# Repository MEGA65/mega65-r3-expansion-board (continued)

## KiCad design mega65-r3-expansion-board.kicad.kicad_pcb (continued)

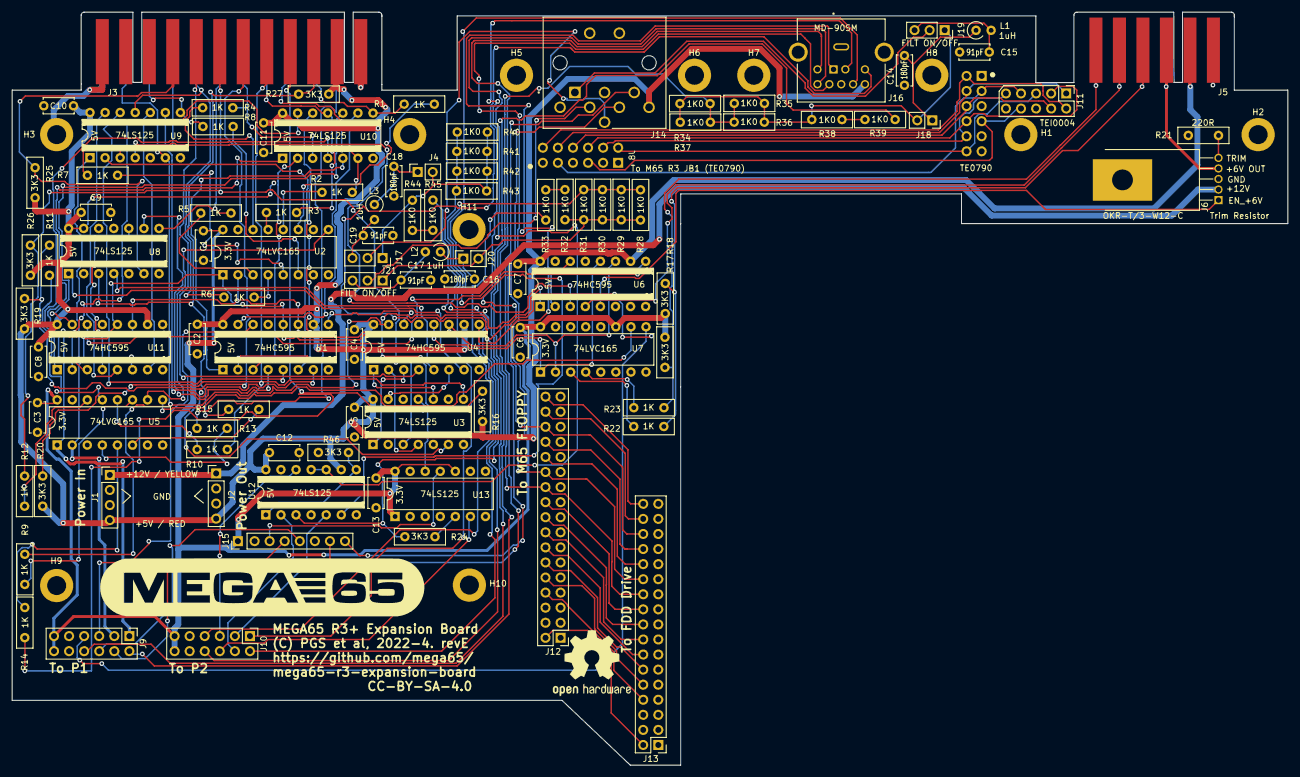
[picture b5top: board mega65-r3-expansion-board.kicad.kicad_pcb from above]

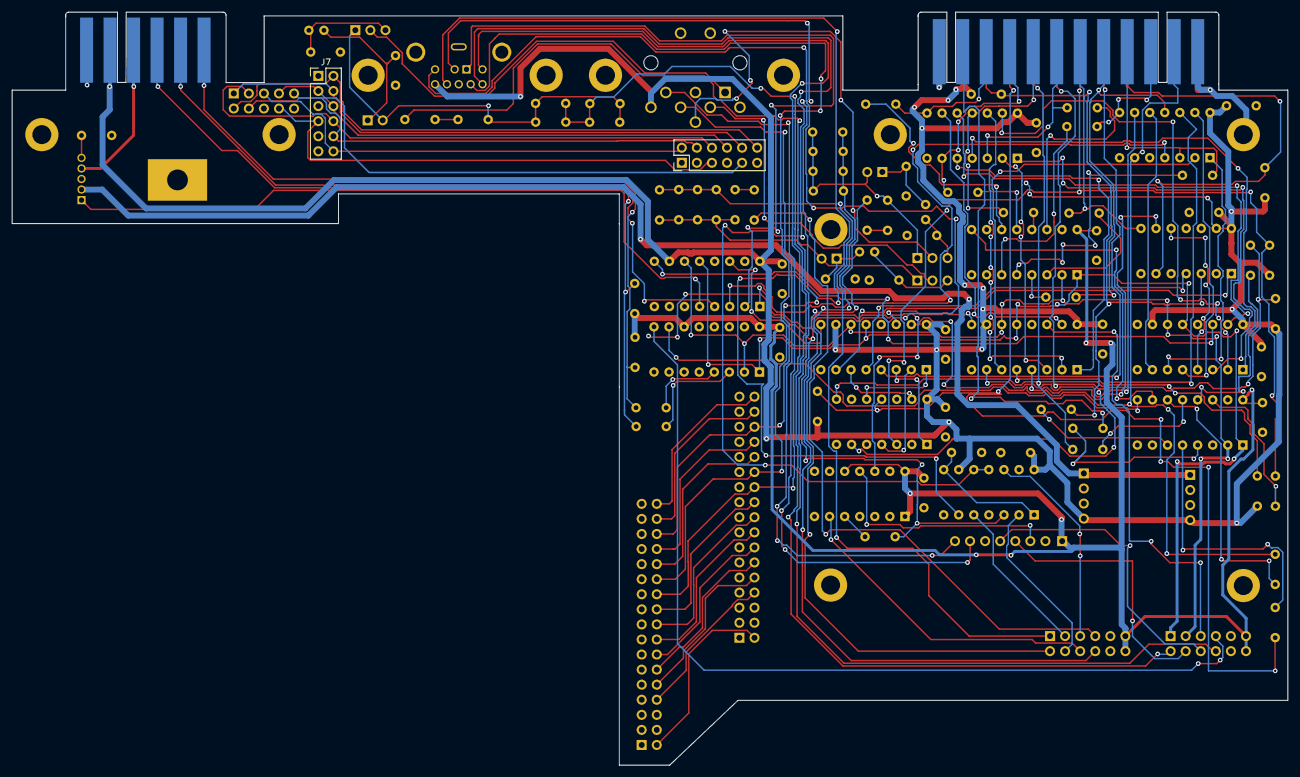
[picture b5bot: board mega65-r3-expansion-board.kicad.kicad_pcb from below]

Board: 4 copper layers, 215.0 x 126.9 mm, 114 parts (2 on the bottom side), 136 nets.

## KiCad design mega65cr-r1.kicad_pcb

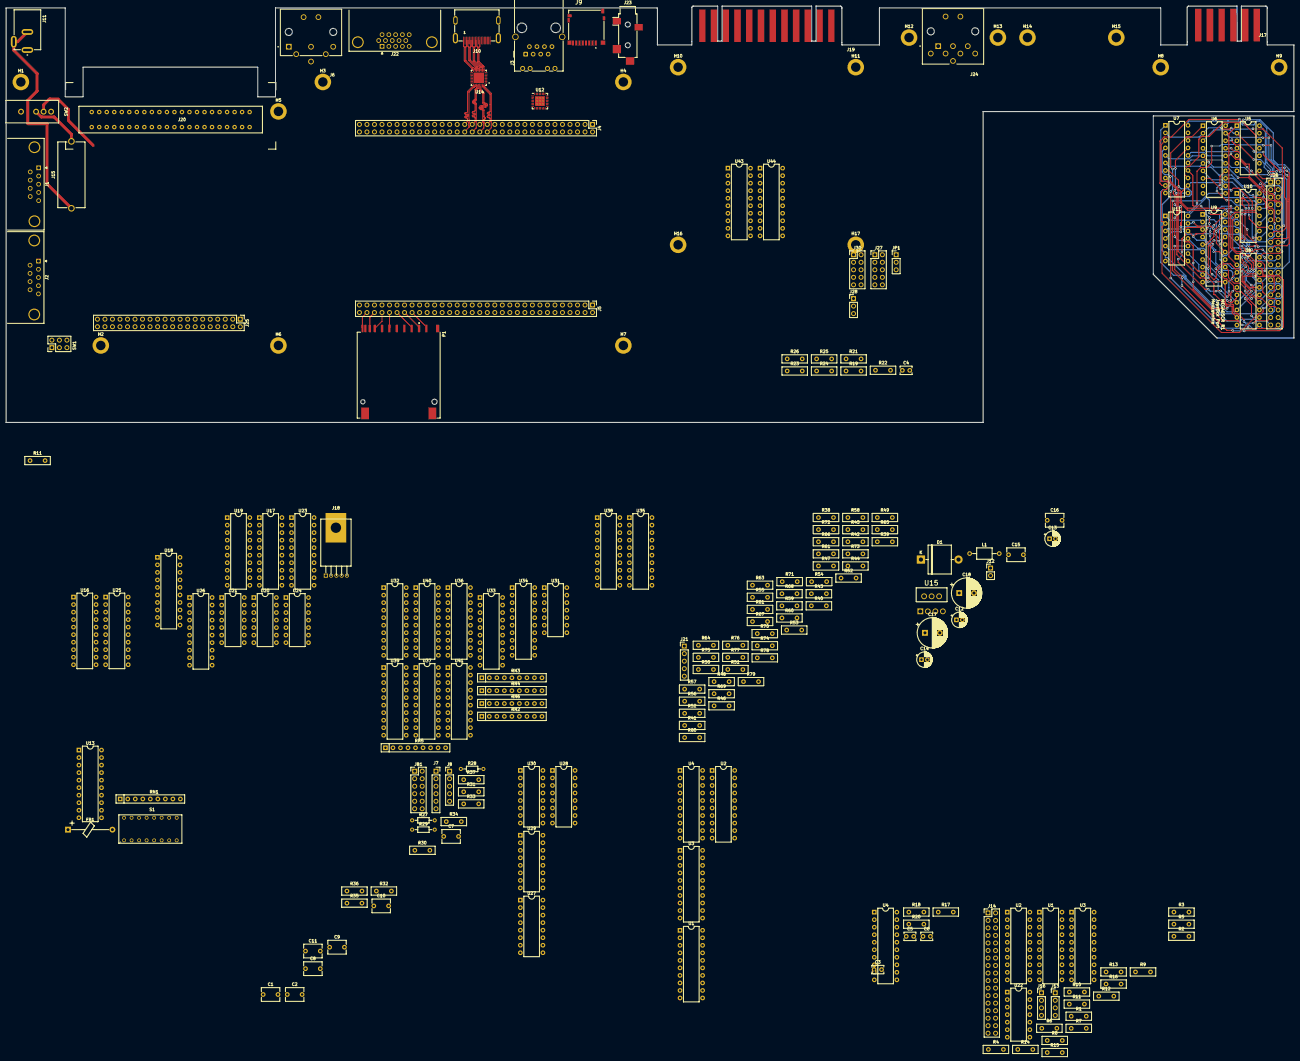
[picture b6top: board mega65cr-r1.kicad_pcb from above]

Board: 4 copper layers, 435.0 x 140.6 mm, 208 parts (0 on the bottom side), 378 nets.

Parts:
C1, C7, C10, C11: 0.1uF; C_Disc_D6.0mm_W4.4mm_P5.00mm
C2: 0.01uF, eg K103Z15Y5VE5TH5; C_Disc_D6.0mm_W4.4mm_P5.00mm
C3, C4, C5, C6: 1.2nF; C_Disc_D3.8mm_W2.6mm_P2.50mm
C8: 1uF; C_Disc_D6.0mm_W4.4mm_P5.00mm
C9: 10uF; C_Disc_D6.0mm_W4.4mm_P5.00mm
C12, C13, C14: 15uF 50V; CP_Radial_D5.0mm_P2.00mm
C15: 0.47uF eg FG28X7R1H474KRT0; C_Disc_D6.0mm_W4.4mm_P5.00mm
C16: 100nF 50V; C_Disc_D6.0mm_W4.4mm_P5.00mm
C17, C18: 180uF 16V; CP_Radial_D10.0mm_P5.00mm
D1: 5V 40V 1N5825; D_5KP_P12.70mm_Horizontal
FB1: FerriteBead FT-3AMB4ARLY-PF; Ferrite_Bead_Axial_L10.0mm_D4.5mm_P15.00mm_Horizontal
H1, H2, H3, H4, H5, H6, H7, H8, H9, H10, H11, H12, H13, H14, H15, H16, H17: MountingHole_Pad; MountingHole_3.2mm_M3_DIN965_Pad
J1, J2: DB9_Male_MountingHoles; DSUB-9_Male_Horizontal_P2.77x2.84mm_EdgePinOffset7.70mm_Hou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
J3: Wuerth_7499010121A; RJ45_Wuerth_7499010121A_Horizontal
J4: QMTECH FPGA Module U4; PinHeader_2x32_P2.54mm_Vertical
J5: QMTECH FPGA Module U5; PinHeader_2x32_P2.54mm_Vertical
J6: SDF-60J for IEC 1541 serial port; CUI_SDF-60J
J7: QMTECH JTAG; PinSocket_1x06_P2.54mm_Vertical
J8: RTC; PinHeader_1x05_P2.54mm_Vertical
J9: 1140084168 microSD Card Slot; AMPHENOL_1140084168
J10: 685119134923
J11: CON-SOCJ-2155; GRAVITECH_CON-SOCJ-2155
J12: Header for power lead to QMTECH WUKONG FPGA board; PinHeader_1x02_P2.54mm_Vertical
J13, J16: Conn_01x04_Male; PinHeader_1x04_P2.54mm_Vertical
J14: Conn_02x17_Odd_Even; PinHeader_2x17_P2.54mm_Vertical
J15: 696101000002 Fuse Holder 20mm; 696101000002
J17: C64_Tape_Port; C64-Cassette-Port-Male
J18: BA60BC0WT; TO-220-FP-5
J19: C64_User_Port; C64-User-Port-Male
J20: C64_Expansion_Port; C64-Cart-Socket-Vertical
J21: Audio Header; PinHeader_1x05_P2.54mm_Vertical
J22: DB15_Female_HighDensity_MountingHoles; DSUB-15-HD_Female_Horizontal_P2.29x1.98mm_EdgePinOffset8.35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
J23: Audio Out; Jack_3.5mm_CUI_SJ-3524-SMT_Horizontal
J24: Component A/V; CUI_SDF-80J
J25: Joystick Ports Mezannine Lower; PinHeader_2x20_P2.54mm_Vertical
J26: Joystick Ports Mezannine Upper; PinHeader_2x20_P2.54mm_Vertical
J27: USB Blaster JTAG; PinHeader_2x05_P2.54mm_Vertical
J28: UART; PinHeader_1x03_P2.54mm_Vertical
J30: Keyboard JTAG header; PinHeader_2x05_P2.54mm_Vertical
JB1: TE0790-03 JTAG + UART; PinHeader_2x06_P2.54mm_Vertical
JP1: KBD JTAG EN; PinHeader_1x03_P2.54mm_Vertical
L1: 22uH, eg SC30R22KT; L_Axial_L5.0mm_D3.6mm_P10.00mm_Horizontal_Murata_BL01RN1A2A2
P1: Full-side CD Card Slot; YAMAICHI_FPS009-2405-0
R1, R2, R3, R4, R5, R6, R7, R8, R9, R10: 1K; R_Box_L8.4mm_W2.5mm_P5.08mm
R11, R11#2, R12, R13, R14, R15, R16, R17, R18, R19, R20, R21, R22, R23, R24, R25, R26, R30, R31, R32, R33, R34, R35, R37: 4K7; R_Box_L8.4mm_W2.5mm_P5.08mm
R27, R28: 220; R_Axial_DIN0204_L3.6mm_D1.6mm_P7.62mm_Horizontal
R29: 6.49K 1%; R_Axial_DIN0204_L3.6mm_D1.6mm_P7.62mm_Horizontal
R36: 12K4; R_Box_L8.4mm_W2.5mm_P5.08mm
R38, R44, R50, R56, R62, R68, R74: 510R; R_Box_L8.4mm_W2.5mm_P5.08mm
R39, R45, R51, R57, R63, R69, R75: 1K0; R_Box_L8.4mm_W2.5mm_P5.08mm
R40, R46, R52, R58, R64, R70, R76: 2K0; R_Box_L8.4mm_W2.5mm_P5.08mm
R41, R47, R53, R59, R65, R71, R77: 4K0; R_Box_L8.4mm_W2.5mm_P5.08mm
R42, R48, R54, R60, R66, R72, R78: 8K0; R_Box_L8.4mm_W2.5mm_P5.08mm
R43, R49, R55, R61, R67, R73, R79: 16K0; R_Box_L8.4mm_W2.5mm_P5.08mm
R80, R81: 49R9; R_Box_L8.4mm_W2.5mm_P5.08mm
RN1, RN3, RN4, RN5, RN6: 3.3K x 8; R_Array_SIP9
RN2: 4609X-AP1-332LF 3.3Kx8; R_Array_SIP9
S1: 418117270908
SW1: Reset Button; SPUJ191500
SW2: SW_SPDT_with_shield; T103J1AVBE2
U1, U1#2, U4, U4#2, U9: 74LS373; DIP-20_W7.62mm
U2, U2#2, U3, U3#2, U6, U7, U13, U16, U17, U23, U32, U33, U34, U38, U39, U43: 74LVC374; DIP-20_W7.62mm
U5, U10, U11, U22: 74LS06N; DIP-14_W7.62mm
U8, U18, U19, U25, U26, U35, U36, U37, U40, U41, U44: 74LS374; DIP-20_W7.62mm
U12: DP83826; QFN-32-1EP_5x5mm_P0.5mm_EP3.3x3.3mm_ThermalVias
U14: PTN3363BSMP; QFN50P500X500X85-33N
U15: LM2678T-5.0; TO127P457X1016X2052-7P
U20, U21, U24: 74LS125; DIP-14_W7.62mm
U27, U28: 74LS138; DIP-16_W7.62mm
U29, U30: 74LS137; DIP-16_W7.62mm
U31: 74LS04; DIP-14_W7.62mm

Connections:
+3V3: FB1.1, J4.3, J4.4, J8.1, J25.2, J26.2, J27.4, J30.4, JB1.6, JP1.1 (A), P1.4 (VDD), R27.1, R28.1, R30.2, R31.2, RN1.1 (common), U2.20 (VCC), U2#2.20 (VCC), U3.20 (VCC), U3#2.20 (VCC), U6.20 (VCC), U7.20 (VCC), U13.20 (VCC), U16.20 (VCC), U17.20 (VCC), U23.20 (VCC), U29.16 (VCC), U32.20 (VCC), U33.20 (VCC), U34.20 (VCC), U38.20 (VCC), U39.20 (VCC), U43.20 (VCC)
+5V: C17.1, C18.1, J1.7, J2.7, J10.18 (+5VPOWER), J13.4, J16.4, J17.2, J17.B, J19.2, J20.2, J20.3, J21.3, J24.8, J25.1, J26.1, L1.2, R11.2, R11#2.2, R17.1, R18.1, R19.1, R20.1, R21.1, R22.1, R23.1, R24.1, R25.1, R26.1, RN2.1 (common), RN3.1 (common), RN4.1 (common), RN5.1 (common), RN6.1 (common), U1.20 (VCC), U1#2.20 (VCC), U4.20 (VCC), U4#2.20 (VCC), U5.14 (VCC), U8.20 (VCC), U9.20 (VCC), U10.14 (VCC), U11.14 (VCC), U14.1 (VDD), U14.18 (VDD), U15.6 (FB), U18.20 (VCC), U19.20 (VCC), U22.14 (VCC), U25.20 (VCC), U26.20 (VCC), U27.6 (E3), U27.16 (VCC), U28.16 (VCC), U29.6 (E3), U31.14 (VCC), U35.20 (VCC), U36.20 (VCC), U37.20 (VCC), U40.20 (VCC), U41.20 (VCC), U44.20 (VCC)
+12V_FUSED: C12.1, C13.1, C14.1, C15.1, J13.1, J16.1, J18.2, SW2.2 (B), U15.2 (VIN), U15.7 (SS)
/Cartridge Port/A0: J20.Y, RN6.9 (R8), U34.3 (D0), U37.19 (O7)
/Cartridge Port/A1: J20.X, RN6.8 (R7), U34.4 (D1), U37.16 (O6)
/Cartridge Port/A2: J20.W, RN6.7 (R6), U34.7 (D2), U37.15 (O5)
/Cartridge Port/A3: J20.V, RN6.6 (R5), U34.8 (D3), U37.12 (O4)
/Cartridge Port/A4: J20.U, RN6.5 (R4), U34.13 (D4), U37.9 (O3)
/Cartridge Port/A5: J20.T, RN6.4 (R3), U34.14 (D5), U37.6 (O2)
/Cartridge Port/A6: J20.S, RN6.3 (R2), U34.17 (D6), U37.5 (O1)
/Cartridge Port/A7: J20.R, RN6.2 (R1), U34.18 (D7), U37.2 (O0)
/Cartridge Port/A8: J20.P, RN5.9 (R8), U39.3 (D0), U41.19 (O7)
/Cartridge Port/A9: J20.N, RN5.8 (R7), U39.4 (D1), U41.16 (O6)
/Cartridge Port/A10: J20.M, RN5.7 (R6), U39.7 (D2), U41.15 (O5)
/Cartridge Port/A11: J20.L, RN5.6 (R5), U39.8 (D3), U41.12 (O4)
/Cartridge Port/A12: J20.K, RN5.5 (R4), U39.13 (D4), U41.9 (O3)
/Cartridge Port/A13: J20.J, RN5.4 (R3), U39.14 (D5), U41.6 (O2)
/Cartridge Port/A14: J20.H, RN5.3 (R2), U39.17 (D6), U41.5 (O1)
/Cartridge Port/A15: J20.F, RN5.2 (R1), U39.18 (D7), U41.2 (O0)
/Cartridge Port/BA: J20.12, U32.18 (D7), U35.19 (O7)
/Cartridge Port/D0: J20.21, RN3.2 (R1), U33.3 (D0), U36.2 (O0)
/Cartridge Port/D1: J20.20, RN3.3 (R2), U33.4 (D1), U36.5 (O1)
/Cartridge Port/D2: J20.19, RN3.4 (R3), U33.7 (D2), U36.6 (O2)
/Cartridge Port/D3: J20.18, RN3.5 (R4), U33.8 (D3), U36.9 (O3)
/Cartridge Port/D4: J20.17, RN3.6 (R5), U33.13 (D4), U36.12 (O4)
/Cartridge Port/D5: J20.16, RN3.7 (R6), U33.14 (D5), U36.15 (O5)
/Cartridge Port/D6: J20.15, RN3.8 (R7), U33.17 (D6), U36.16 (O6)
/Cartridge Port/D7: J20.14, RN3.9 (R8), U33.18 (D7), U36.19 (O7)
/Cartridge Port/DMA_N: J20.13, RN4.5 (R4), U32.13 (D4)
/Cartridge Port/DOTCLOCK: J20.6, U31.2, U38.7 (D2)
/Cartridge Port/EXROM_N: J20.9, RN2.4 (R3), U38.14 (D5), U40.15 (O5)
/Cartridge Port/GAME_N: J20.8, RN2.5 (R4), U38.13 (D4), U40.12 (O4)
/Cartridge Port/IO1_N: J20.7, RN2.6 (R5), U38.8 (D3), U40.9 (O3)
/Cartridge Port/IO2_N: J20.10, RN2.3 (R2), U38.17 (D6), U40.16 (O6)
/Cartridge Port/IRQ_N: J20.4, RN2.9 (R8), RN4.8 (R7), U32.4 (D1)
/Cartridge Port/PHI2: J20.E, U38.18 (D7), U40.19 (O7)
/Cartridge Port/RESET_N: J20.C, RN4.9 (R8), U32.3 (D0)
/Cartridge Port/ROMH_N: J20.B, U32.17 (D6), U35.16 (O6)
/Cartridge Port/ROML_N: J20.11, RN2.2 (R1), U32.14 (D5), U35.15 (O5)
/Cartridge Port/R_W: J20.5, RN2.8 (R7), RN4.6 (R5), U32.8 (D3)
/FPGA Module/VCCO_12_13: J5.3, J5.4
/FPGA Module/VIN: J4.63, J4.64, J5.63, J5.64
/IEC & 3.5" Drives/DIR: J14.18, U1.9 (O3), U1#2.9 (O3)
/IEC & 3.5" Drives/DISKCHG: J14.34, R10.1, R15.1
/IEC & 3.5" Drives/DRVSA: J14.14, U1.6 (O2), U1#2.6 (O2)
/IEC & 3.5" Drives/DRVSB: J14.12, U4.15 (O5), U4#2.15 (O5)
/IEC & 3.5" Drives/INDEX: J14.8, R6.1, R12.2
/IEC & 3.5" Drives/MOTEA: J14.10, U1.5 (O1), U1#2.5 (O1)
/IEC & 3.5" Drives/RDATA: J14.30, R9.1, R16.1
/IEC & 3.5" Drives/REDWC: J14.2, U1.2 (O0), U1#2.2 (O0)
/IEC & 3.5" Drives/SER_ATN_OUT: U4.12 (O4), U4#2.12 (O4), U22.9
/IEC & 3.5" Drives/SER_CLK: J6.4, R3.1, U22.4
/IEC & 3.5" Drives/SER_CLK_OUT: U4.6 (O2), U4#2.6 (O2), U22.3
/IEC & 3.5" Drives/SER_DATA: J6.5, R4.1, U22.12
/IEC & 3.5" Drives/SER_DATA_OUT: U4.9 (O3), U4#2.9 (O3), U22.13
/IEC & 3.5" Drives/SER_RESET: J6.6, R1.1, U22.6
/IEC & 3.5" Drives/SER_RESET_OUT: U4.2 (O0), U4#2.2 (O0), U22.5
/IEC & 3.5" Drives/SER_SEQ_OUT: U4.5 (O1), U4#2.5 (O1)
/IEC & 3.5" Drives/SER_SRQ: J6.1, R2.1, U22.10
/IEC & 3.5" Drives/SIDE1: J14.32, U1.19 (O7), U1#2.19 (O7)
/IEC & 3.5" Drives/STEP: J14.20, U1.12 (O4), U1#2.12 (O4)
/IEC & 3.5" Drives/TRCK0: J14.26, R7.1, R13.1
/IEC & 3.5" Drives/WDATA: J14.22, U1.15 (O5), U1#2.15 (O5)
/IEC & 3.5" Drives/WGATE: J14.24, U1.16 (O6), U1#2.16 (O6)
/IEC & 3.5" Drives/WPROT: J14.28, R8.1, R14.1
/Joystick Ports/JA_AX: C3.2, J1.9, J25.15
/Joystick Ports/JA_AY: C5.2, J1.5, J25.17
/Joystick Ports/JA_DOWN: J1.2, J25.9, R19.2
/Joystick Ports/JA_FIRE: J1.6, J25.7, R20.2
/Joystick Ports/JA_LEFT: J1.3, J25.11, R18.2
/Joystick Ports/JA_RIGHT: J1.4, J25.13, R17.2
/Joystick Ports/JA_UP: J1.1, J25.5, R21.2
/Joystick Ports/JB_AX: C4.2, J2.9, J25.31
/Joystick Ports/JB_AY: C6.2, J2.5, J25.33
/Joystick Ports/JB_DOWN: J2.2, J25.25, R24.2
/Joystick Ports/JB_FIRE: J2.6, J25.23, R25.2
/Joystick Ports/JB_LEFT: J2.3, J25.27, R23.2
/Joystick Ports/JB_RIGHT: J2.4, J25.29, R22.2
/Joystick Ports/JB_UP: J2.1, J25.21, R26.2
/Joystick Ports/M_JA_AX: J26.15, U5.4, U6.4 (D1)
/Joystick Ports/M_JA_AY: J26.17, U5.2, U6.3 (D0)
/Joystick Ports/M_JA_DOWN: J26.9, U6.13 (D4), U10.10
/Joystick Ports/M_JA_FIRE: J26.7, U6.14 (D5), U10.12
/Joystick Ports/M_JA_LEFT: J26.11, U6.8 (D3), U10.8
/Joystick Ports/M_JA_RIGHT: J26.13, U6.7 (D2), U10.6
/Joystick Ports/M_JA_UP: J26.5, U6.17 (D6), U10.2
/Joystick Ports/M_JB_AX: J26.31, U7.4 (D1), U10.4
/Joystick Ports/M_JB_AY: J26.33, U7.3 (D0), U11.2
/Joystick Ports/M_JB_DOWN: J26.25, U7.13 (D4), U11.10
/Joystick Ports/M_JB_FIRE: J26.23, U7.14 (D5), U11.12
/Joystick Ports/M_JB_LEFT: J26.27, U7.8 (D3), U11.8
/Joystick Ports/M_JB_RIGHT: J26.29, U7.7 (D2), U11.6
/Joystick Ports/M_JB_UP: J26.21, U7.17 (D6), U11.4
/Joystick Ports/M_MUX_DI0: J26.6, U6.2 (O0), U7.2 (O0)
/Joystick Ports/M_MUX_DI1: J26.8, U6.5 (O1), U7.5 (O1)
/Joystick Ports/M_MUX_DI2: J26.10, U6.6 (O2), U7.6 (O2)
/Joystick Ports/M_MUX_DI3: J26.12, U7.9 (O3)
/Joystick Ports/M_MUX_DI4: J26.20, U6.12 (O4), U7.12 (O4)
/Joystick Ports/M_MUX_DI5: J26.18, U6.15 (O5), U7.15 (O5)
/Joystick Ports/M_MUX_DI6: J26.16, U6.16 (O6), U7.16 (O6)
/Joystick Ports/M_MUX_DI7: J26.14, U6.19 (O7)
/Joystick Ports/M_MUX_DO0: J26.22, U8.3 (D0), U9.3 (D0)
/Joystick Ports/M_MUX_DO1: J26.24, U8.4 (D1), U9.4 (D1)
/Joystick Ports/M_MUX_DO2: J26.26, U8.7 (D2), U9.7 (D2)
/Joystick Ports/M_MUX_DO3: J26.28, U8.8 (D3), U9.8 (D3)
/Joystick Ports/M_MUX_DO4: J26.30, U8.14 (D5), U9.13 (D4)
/Joystick Ports/M_MUX_DO5: J26.32, U8.13 (D4), U9.14 (D5)
/Joystick Ports/M_MUX_DO6: J26.34, U8.17 (D6), U9.17 (D6)
/Joystick Ports/M_MUX_DO7: J26.36, U8.18 (D7), U9.18 (D7)
/Joystick Ports/M_MUX_SEL_2: J26.38, U6.11 (Cp), U8.11 (Cp)
/Joystick Ports/M_MUX_SEL_2_N: J26.40, U6.1 (OE)
/Joystick Ports/M_MUX_SEL_3: J26.37, U7.11 (Cp), U9.11 (LE)
/Joystick Ports/M_MUX_SEL_3_N: J26.39, U7.1 (OE)
/Joystick Ports/M_RESET_BTN: J26.19, U6.18 (D7)
/Joystick Ports/RESET_BTN: J25.19, R11.1, R11#2.1, SW1.3 (C), SW1.6 (C)
/MEGA65 Peripherals, DVI, Eth, microSD/CK+: J10.10 (TMDSCLOCK+), U14.10 (OUT_D4-)
/MEGA65 Peripherals, DVI, Eth, microSD/CK-: J10.12 (TMDSCLOCK-), U14.9 (OUT_D4+)
/MEGA65 Peripherals, DVI, Eth, microSD/D0+: J10.7 (TMDSDATA0+), U14.12 (OUT_D3-)
/MEGA65 Peripherals, DVI, Eth, microSD/D0-: J10.9 (TMDSDATA0-), U14.11 (OUT_D3+)
/MEGA65 Peripherals, DVI, Eth, microSD/D1+: J10.4 (TMDSDATA1+), U14.14 (OUT_D2-)
/MEGA65 Peripherals, DVI, Eth, microSD/D1-: J10.6 (TMDSDATA1-), U14.13 (OUT_D2+)
/MEGA65 Peripherals, DVI, Eth, microSD/D2+: J10.1 (TMDSDATA2+), U14.16 (OUT_D1-)
/MEGA65 Peripherals, DVI, Eth, microSD/D2-: J10.3 (TMDSDATA2-), U14.15 (OUT_D1+)
/MEGA65 Peripherals, DVI, Eth, microSD/DIP1: RN1.2 (R1), S1.A1, U13.3 (D0)
/MEGA65 Peripherals, DVI, Eth, microSD/DIP2: RN1.3 (R2), S1.A2, U13.4 (D1)
/MEGA65 Peripherals, DVI, Eth, microSD/DIP3: RN1.4 (R3), S1.A3, U13.7 (D2)
/MEGA65 Peripherals, DVI, Eth, microSD/DIP4: RN1.5 (R4), S1.A4, U13.8 (D3)
/MEGA65 Peripherals, DVI, Eth, microSD/DIP5: RN1.6 (R5), S1.A5, U13.13 (D4)
/MEGA65 Peripherals, DVI, Eth, microSD/DIP6: RN1.7 (R6), S1.A6, U13.14 (D5)
/MEGA65 Peripherals, DVI, Eth, microSD/DIP7: RN1.8 (R7), S1.A7, U13.17 (D6)
/MEGA65 Peripherals, DVI, Eth, microSD/DIP8: RN1.9 (R8), S1.A8, U13.18 (D7)
/MEGA65 Peripherals, DVI, Eth, microSD/ETH_RX_N: J3.6 (RD-), U12.4 (RXN)
/MEGA65 Peripherals, DVI, Eth, microSD/ETH_RX_P: J3.4 (RD+), U12.5 (RXP)
/MEGA65 Peripherals, DVI, Eth, microSD/ETH_TX_N: J3.3 (TD-), U12.6 (TXN)
/MEGA65 Peripherals, DVI, Eth, microSD/ETH_TX_P: J3.1 (TD+), U12.7 (TXP)
/MEGA65 Peripherals, DVI, Eth, microSD/HPD_B: J10.19 (HOTPLUGDETECT/HEAC-), U14.21 (HPD_B)
/MEGA65 Peripherals, DVI, Eth, microSD/SCL_B: J10.15 (SCL), U14.19 (SCL_SINK)
/MEGA65 Peripherals, DVI, Eth, microSD/SDA_B: J10.16 (SDA), U14.20 (SDA_SINK)
/Power Supply & Mounting Holes/VBAT: J11.2, J11.3, J15.1
/User Port/6V_REG_CTL: J18.1, U17.7 (D2), U19.6 (O2)
/User Port/CNT1: J19.4, U16.7 (D2), U18.6 (O2)
/User Port/CNT2: J19.6, U16.13 (D4), U18.12 (O4)
/User Port/DATA_0: J19.C, U21.3, U23.3 (D0)
/User Port/DATA_0_O: U21.2, U26.2 (O0)
/User Port/DATA_1: J19.D, U21.6, U23.4 (D1)
/User Port/DATA_1_O: U21.5, U26.5 (O1)
/User Port/DATA_2: J19.E, U21.8, U23.7 (D2)
/User Port/DATA_2_O: U21.9, U26.6 (O2)
/User Port/DATA_3: J19.F, U21.11, U23.8 (D3)
/User Port/DATA_3_O: U21.12, U26.9 (O3)
/User Port/DATA_4: J19.H, U23.13 (D4), U24.3
/User Port/DATA_4_O: U24.2, U26.12 (O4)
/User Port/DATA_5: J19.J, U23.14 (D5), U24.6
/User Port/DATA_5_O: U24.5, U26.15 (O5)
/User Port/DATA_6: J19.K, U23.17 (D6), U24.8
/User Port/DATA_6_O: U24.9, U26.16 (O6)
/User Port/DATA_7: J19.L, U23.18 (D7), U24.11
/User Port/DATA_7_O: U24.12, U26.19 (O7)
/User Port/EN_DATA_0: U21.1, U25.2 (O0)
/User Port/EN_DATA_1: U21.4, U25.5 (O1)
/User Port/EN_DATA_2: U21.10, U25.6 (O2)
/User Port/EN_DATA_3: U21.13, U25.9 (O3)
/User Port/EN_DATA_4: U24.1, U25.12 (O4)
/User Port/EN_DATA_5: U24.4, U25.15 (O5)
/User Port/EN_DATA_6: U24.10, U25.16 (O6)
/User Port/EN_DATA_7: U24.13, U25.19 (O7)
/User Port/EN_PA2: U19.19 (O7), U20.4
/User Port/EN_RESET_N: U18.5 (O1), U20.1
/User Port/FLAG2: J19.B, U16.18 (D7), U18.19 (O7)
/User Port/PA2: J19.M, U17.17 (D6), U20.6
/User Port/PA2_O: U19.16 (O6), U20.5
/User Port/PC2: J19.8, U16.17 (D6), U18.16 (O6)
/User Port/RESET_N: J19.3, U16.3 (D0), U20.3
/User Port/RESET_N_O: U18.2 (O0), U20.2
/User Port/SP1: J19.5, U16.8 (D3), U18.9 (O3)
/User Port/SP2: J19.7, U16.14 (D5), U18.15 (O5)
/User Port/TAPE_READ: J17.4, J17.D, U17.3 (D0)
/User Port/TAPE_SENSE: J17.6, J17.F, U17.4 (D1)
/User Port/TAPE_WRITE: J17.5, J17.E, U19.9 (O3)
/VGA, C64 AV & C64 Keyboard/COMP_CHROMA: J24.6, R56.2, R57.2, R58.2, R59.2, R60.2
/VGA, C64 AV & C64 Keyboard/COMP_LUMA: J24.1, J24.4, R50.2, R51.2, R52.2, R53.2, R54.2
/VGA, C64 AV & C64 Keyboard/VGA_B: J22.3, R74.2, R75.2, R76.2, R77.2, R78.2
/VGA, C64 AV & C64 Keyboard/VGA_G: J22.2, R68.2, R69.2, R70.2, R71.2, R72.2
/VGA, C64 AV & C64 Keyboard/VGA_R: J22.1, R62.2, R63.2, R64.2, R65.2, R66.2
AUDIO_L: J21.2, J23.T, J24.3, R38.2, R39.2, R40.2, R41.2, R42.2
AUDIO_L0: J5.29, R43.1
AUDIO_L1: J5.27, R42.1
AUDIO_L2: J5.25, R41.1
AUDIO_L3: J5.23, R40.1
AUDIO_L4: J5.21, R39.1
AUDIO_L5: J5.19, R38.1
AUDIO_R: J21.4, J23.R, R44.2, R45.2, R46.2, R47.2, R48.2
AUDIO_R0: J5.17, R49.1
AUDIO_R1: J5.15, R48.1
AUDIO_R2: J5.13, R47.1
AUDIO_R3: J5.11, R46.1
AUDIO_R4: J5.9, R45.1
AUDIO_R5: J5.7, R44.1
COMP_CHROMA0: J5.18, R61.1
COMP_CHROMA1: J5.16, R60.1
COMP_CHROMA2: J5.14, R59.1
COMP_CHROMA3: J5.12, R58.1
COMP_CHROMA4: J5.10, R57.1
COMP_CHROMA5: J5.8, R56.1
COMP_LUMA0: J5.30, R55.1
COMP_LUMA1: J5.28, R54.1
COMP_LUMA2: J5.26, R53.1
COMP_LUMA3: J5.24, R52.1
COMP_LUMA4: J5.22, R51.1
COMP_LUMA5: J5.20, R50.1
DOTCLOCK_O: J4.60, U31.1
ETH_CLKIN: J4.24, U12.9 (XI/CLKIN)
ETH_COL_DETECT: J4.18, U12.28 (COL/~MII_MODE4)
ETH_LED_GREEN: J3.9, U12.31 (LED1/~100_SEL)
ETH_LED_YELLOW: J3.11, U12.30 (LED0/~AUTO_NEG_EN)
ETH_MDC: J4.22, U12.12 (MDC)
ETH_MDIO: J4.20, U12.11 (MDIO)
ETH_POWERDOWN: U12.21 (~INT), U19.12 (O4)
ETH_RESET: U12.32 (~RST), U19.15 (O5)
ETH_RX_CLK: J4.14, U12.19 (RX_CLK)
ETH_RX_D0: J4.21, U12.16 (RXD0/~HF_DX/_FULL_DX)
ETH_RX_D1: J4.23, U12.15 (RXD1/~PHY_ADD2)
ETH_RX_DV: J4.25, U12.18 (RX_DV/~MII_MODE10)
ETH_RX_ER: J4.16, U12.20 (RX_ER/~MII_ISOL_EN)
ETH_TX_CLK: J4.19, U12.22 (TX_CLK)
ETH_TX_D0: J4.13, U12.24 (TXD0)
ETH_TX_D1: J4.15, U12.25 (TXD1)
ETH_TX_EN: J4.17, U12.23 (TX_EN)
GND: C1.2, C2.2, C3.1, C4.1, C5.1, C6.1, C7.2, C8.2, C9.2, C10.2, C11.2, C12.2, C13.2, C14.2, C15.2, C17.2, C18.2, D1.2 (A), H1.1, H2.1, H3.1, H4.1, H5.1, H6.1, H7.1, H8.1, H9.1, H10.1, H11.1, H12.1, H13.1, H14.1, H15.1, H16.1, H17.1, J1.0 (PAD), J1.8, J2.0 (PAD), J2.8, J3.8, J3.SH, J4.1, J4.2, J4.5, J4.6, J4.61, J4.62, J5.1, J5.2, J5.5, J5.6, J5.61, J5.62, J6.2, J6.S1 (SHIELD), J6.S2 (SHIELD), J7.2, J8.5, J9.6 (SUPPLY_VOLTAGE_GROUND), J9.10 (CD_SWITCH2), J9.S1 (SHIELD), J9.S2 (SHIELD), J9.S3 (SHIELD), J9.S4 (SHIELD), J10.2 (TMDSDATA2SHIELD), J10.5 (TMDSDATA1SHIELD), J10.8 (TMDSDATA0SHIELD), J10.11 (TMDSCLOCKSHIELD), J10.17 (DDC/CECGROUND), J10.SHELL, J10.SHELL1, J10.SHELL2, J10.SHELL3, J13.2, J13.3, J14.1, J14.3, J14.5, J14.7, J14.9, J14.11, J14.13, J14.15, J14.17, J14.19, J14.21, J14.23, J14.25, J14.27, J14.29, J14.31, J14.33, J16.2, J16.3, J18.3, J18.6, J19.1, J19.12, J19.A, J19.N, J20.1, J20.22, J20.A, J20.Z, J21.1, J21.5, J22.0, J22.5, J22.6, J22.7, J22.8, J22.10, J23.S, J24.2, J24.S1 (Shield), J24.S2 (Shield), J25.3, J25.4, J26.3, J26.4, J27.2, J27.10, J28.1, J30.2, J30.10, JB1.1, JB1.2, JP1.3 (B), P1.3 (VSS1), P1.6 (VSS2), P1.11 (COM), R29.2, R32.2, R33.2, R34.2, R35.2, R36.1, S1.1, S1.2, S1.3, S1.4, S1.5, S1.6, S1.7, S1.8, SW1.2 (B), SW1.5 (B), SW2.SH (SHIELD), U1.1 (OE), U1.10 (GND), U1#2.1 (OE), U1#2.10 (GND), U2.10 (GND), U2#2.10 (GND), U3.10 (GND), U3#2.10 (GND), U4.1 (OE), U4.10 (GND), U4#2.1 (OE), U4#2.10 (GND), U5.5, U5.7 (GND), U5.9, U5.11, U5.13, U6.10 (GND), U7.10 (GND), U8.1 (OE), U8.10 (GND), U9.1 (OE), U9.10 (GND), U10.7 (GND), U11.7 (GND), U12.1 (ENHANCED/~BASIC), U12.33 (GND/Thermal_Pad), U13.10 (GND), U14.33 (GND), U15.4 (GND), U16.10 (GND), U17.10 (GND), U18.1 (OE), U18.10 (GND), U19.1 (OE), U19.10 (GND), U20.10, U20.13, U22.1, U22.7 (GND), U23.10 (GND), U25.1 (OE), U25.10 (GND), U26.1 (OE), U26.10 (GND), U27.4 (E1), U27.8 (GND), U28.4 (E1), U28.5 (E2), U28.8 (GND), U29.4 (E1), U29.8 (GND), U30.4 (E1), U30.5 (E2), U30.8 (GND), U31.3, U31.5, U31.9, U31.11, U31.13, U32.10 (GND), U33.10 (GND), U34.10 (GND), U35.1 (OE), U35.10 (GND), U36.1 (OE), U36.10 (GND), U37.1 (OE), U37.10 (GND), U38.10 (GND), U39.10 (GND), U40.1 (OE), U40.10 (GND), U41.1 (OE), U41.10 (GND), U43.10 (GND), U44.1 (OE), U44.10 (GND)
HDMI_CK+: J4.29, U14.31 (IN_D4-)
HDMI_CK-: J4.30, U14.32 (IN_D4+)
HDMI_D0+: J4.31, U14.29 (IN_D3-)
HDMI_D0-: J4.32, U14.30 (IN_D3+)
HDMI_D1+: J4.33, U14.27 (IN_D2-)
HDMI_D1-: J4.34, U14.28 (IN_D2+)
HDMI_D2+: J4.35, U14.25 (IN_D1-)
HDMI_D2-: J4.36, U14.26 (IN_D1+)
HDMI_HIZ_EN: U14.24 (HIZ_EN), U19.2 (O0)
HDMI_HPD: J4.26, U14.5 (HPD_SOURCE)
HDMI_OE_N: U14.17 (/OE), U19.5 (O1)
HDMI_SCL: J4.27, U14.7 (SCL_SOURCE)
HDMI_SDA: J4.28, U14.6 (SDA_SOURCE)
IEC_ATN: J6.3, J19.9, R5.1, U22.8
JTAG_TCK: J7.3, J27.1, JB1.4
JTAG_TDI: J7.5, J27.9, JB1.10
JTAG_TDO: J7.4, J27.3, JB1.8
JTAG_TMS: J7.6, J27.5, JB1.12
MUX_A0: J5.47, U27.1 (A0), U28.1 (A0), U29.1 (A0), U30.1 (A0)
MUX_A1: J5.49, U27.2 (A1), U28.2 (A1), U29.2 (A1), U30.2 (A1)
MUX_A2: J5.51, U27.3 (A2), U28.3 (A2), U29.3 (A2), U30.3 (A2)
MUX_A3: J5.53, U27.5 (E2), U28.6 (E3), U29.5 (E2), U30.6 (E3)
MUX_DI0: J5.31, J25.6, U2.2 (O0), U2#2.2 (O0), U3.2 (O0), U3#2.2 (O0), U13.2 (O0), U16.2 (O0), U17.2 (O0), U23.2 (O0), U32.2 (O0), U33.2 (O0), U34.2 (O0), U38.2 (O0), U39.2 (O0), U43.2 (O0)
MUX_DI1: J5.33, J25.8, U2.5 (O1), U2#2.5 (O1), U3.5 (O1), U3#2.5 (O1), U13.5 (O1), U17.5 (O1), U23.5 (O1), U32.5 (O1), U33.5 (O1), U34.5 (O1), U38.5 (O1), U39.5 (O1), U43.5 (O1)
MUX_DI2: J5.35, J25.10, U2.6 (O2), U2#2.6 (O2), U3.6 (O2), U3#2.6 (O2), U13.6 (O2), U16.6 (O2), U17.6 (O2), U23.6 (O2), U32.6 (O2), U33.6 (O2), U34.6 (O2), U38.6 (O2), U39.6 (O2), U43.6 (O2)
MUX_DI3: J5.37, J25.12, U2.9 (O3), U2#2.9 (O3), U3.9 (O3), U3#2.9 (O3), U13.9 (O3), U16.9 (O3), U17.9 (O3), U23.9 (O3), U32.9 (O3), U33.9 (O3), U34.9 (O3), U38.9 (O3), U39.9 (O3), U43.9 (O3)
MUX_DI4: J5.39, J25.20, U2.12 (O4), U2#2.12 (O4), U3.12 (O4), U3#2.12 (O4), U13.12 (O4), U16.12 (O4), U17.12 (O4), U23.12 (O4), U32.12 (O4), U33.12 (O4), U34.12 (O4), U38.12 (O4), U39.12 (O4), U43.12 (O4)
MUX_DI5: J5.41, J25.18, U13.15 (O5), U16.15 (O5), U17.15 (O5), U23.15 (O5), U32.15 (O5), U33.15 (O5), U34.15 (O5), U38.15 (O5), U39.15 (O5), U43.15 (O5)
MUX_DI6: J5.43, J25.16, U13.16 (O6), U16.16 (O6), U17.16 (O6), U23.16 (O6), U32.16 (O6), U33.16 (O6), U34.16 (O6), U38.16 (O6), U39.16 (O6), U43.16 (O6)
MUX_DI7: J5.45, J25.14, U13.19 (O7), U16.19 (O7), U23.19 (O7), U32.19 (O7), U33.19 (O7), U34.19 (O7), U38.19 (O7), U39.19 (O7), U43.19 (O7)
MUX_DO0: J5.32, J25.22, U1.3 (D0), U1#2.3 (D0), U4.3 (D0), U4#2.3 (D0), U18.3 (D0), U19.3 (D0), U25.3 (D0), U26.3 (D0), U35.3 (D0), U36.3 (D0), U37.3 (D0), U40.3 (D0), U41.3 (D0), U44.3 (D0)
MUX_DO1: J5.34, J25.24, U1.4 (D1), U1#2.4 (D1), U4.4 (D1), U4#2.4 (D1), U18.4 (D1), U19.4 (D1), U25.4 (D1), U26.4 (D1), U35.4 (D1), U36.4 (D1), U37.4 (D1), U40.4 (D1), U41.4 (D1), U44.4 (D1)
MUX_DO2: J5.36, J25.26, U1.7 (D2), U1#2.7 (D2), U4.7 (D2), U4#2.7 (D2), U18.7 (D2), U19.7 (D2), U25.7 (D2), U26.7 (D2), U35.7 (D2), U36.7 (D2), U37.7 (D2), U40.7 (D2), U41.7 (D2), U44.7 (D2)
MUX_DO3: J5.38, J25.28, U1.8 (D3), U1#2.8 (D3), U4.8 (D3), U4#2.8 (D3), U18.8 (D3), U19.8 (D3), U25.8 (D3), U26.8 (D3), U35.8 (D3), U36.8 (D3), U37.8 (D3), U40.8 (D3), U41.8 (D3), U44.8 (D3)
MUX_DO4: J5.40, J25.30, U1.13 (D4), U1#2.13 (D4), U4.13 (D4), U4#2.13 (D4), U18.13 (D4), U19.13 (D4), U25.13 (D4), U26.13 (D4), U35.13 (D4), U36.13 (D4), U37.13 (D4), U40.13 (D4), U41.13 (D4), U44.13 (D4)
MUX_DO5: J5.42, J25.32, U1.14 (D5), U1#2.14 (D5), U4.14 (D5), U4#2.14 (D5), U18.14 (D5), U19.14 (D5), U25.14 (D5), U26.14 (D5), U35.14 (D5), U36.14 (D5), U37.14 (D5), U40.14 (D5), U41.14 (D5), U44.14 (D5)
MUX_DO6: J5.44, J25.34, U1.17 (D6), U1#2.17 (D6), U18.17 (D6), U19.17 (D6), U25.17 (D6), U26.17 (D6), U35.17 (D6), U36.17 (D6), U37.17 (D6), U40.17 (D6), U41.17 (D6), U44.17 (D6)
MUX_DO7: J5.46, J25.36, U1.18 (D7), U1#2.18 (D7), U18.18 (D7), U19.18 (D7), U25.18 (D7), U26.18 (D7), U35.18 (D7), U36.18 (D7), U37.18 (D7), U40.18 (D7), U41.18 (D7), U44.18 (D7)
MUX_LATCH_0: U1.11 (LE), U1#2.11 (LE), U2.11 (Cp), U2#2.11 (Cp)
MUX_LATCH_0_N: U2.1 (OE), U2#2.1 (OE)
MUX_LATCH_1: U3.11 (Cp), U3#2.11 (Cp), U4.11 (LE), U4#2.11 (LE)
MUX_LATCH_1_N: U3.1 (OE), U3#2.1 (OE)
MUX_SEL_2: J25.38, U27.13 (O2)
MUX_SEL_2_N: J25.40, U29.13 (O2)
MUX_SEL_3: J25.37, U27.12 (O3)
MUX_SEL_3_N: J25.39, U29.12 (O3)
MUX_SEL_4: U17.11 (Cp), U19.11 (Cp), U27.11 (O4)
MUX_SEL_4_N: U17.1 (OE), U29.11 (O4)
MUX_SEL_5: U16.11 (Cp), U18.11 (Cp), U27.10 (O5)
MUX_SEL_5_N: U16.1 (OE), U29.10 (O5)
MUX_SEL_6: U23.11 (Cp), U26.11 (Cp), U27.9 (O6)
MUX_SEL_6_N: U23.1 (OE), U29.9 (O6)
MUX_SEL_7: U25.11 (Cp), U27.7 (O7)
MUX_SEL_8: U13.11 (Cp), U28.15 (O0)
MUX_SEL_8_N: U13.1 (OE), U30.15 (O0)
MUX_SEL_9: U28.14 (O1), U33.11 (Cp), U36.11 (Cp)
MUX_SEL_9_N: U30.14 (O1), U33.1 (OE)
MUX_SEL_10: U28.13 (O2), U38.11 (Cp), U40.11 (Cp)
MUX_SEL_10_N: U30.13 (O2), U38.1 (OE)
MUX_SEL_11: U28.12 (O3), U34.11 (Cp), U37.11 (Cp)
MUX_SEL_11_N: U30.12 (O3), U34.1 (OE)
MUX_SEL_12: U28.11 (O4), U39.11 (Cp), U41.11 (Cp)
MUX_SEL_12_N: U30.11 (O4), U39.1 (OE)
MUX_SEL_13: U28.10 (O5), U32.11 (Cp), U35.11 (Cp)
MUX_SEL_13_N: U30.10 (O5), U32.1 (OE)
MUX_SEL_14: U28.9 (O6), U43.11 (Cp), U44.11 (Cp)
MUX_SEL_14_N: U30.9 (O6), U43.1 (OE)
NMI_N: J20.D, RN4.7 (R6), U32.7 (D2)
unnamed: C1.1, U12.2 (CEXT)
unnamed: C2.1, C7.1, C8.1, C9.1, FB1.2, U12.3 (VDDA3V3), U12.17 (VDDIO)
unnamed: C10.1, J3.2 (TCT)
unnamed: C11.1, J3.5 (RCT)
unnamed: C16.1, U15.3 (BOOST)
unnamed: C16.2, D1.1 (K), L1.1, U15.1 (SW)
unnamed: J3.10, R27.2
unnamed: J3.12, R28.2
unnamed: J9.4 (SUPPLY_VOLTAGE), R37.2
unnamed: J17.1, J17.A
unnamed: J17.3, J17.C, J18.4
unnamed: J22.13, R80.1
unnamed: J22.14, R81.1
unnamed: R1.2, U3.3 (D0), U3#2.3 (D0)
unnamed: R2.2, U3.4 (D1), U3#2.4 (D1)
unnamed: R3.2, U3.7 (D2), U3#2.7 (D2)
unnamed: R4.2, U3.8 (D3), U3#2.8 (D3)
unnamed: R5.2, U3.13 (D4), U3#2.13 (D4)
unnamed: R6.2, U2.3 (D0), U2#2.3 (D0)
unnamed: R7.2, U2.4 (D1), U2#2.4 (D1)
unnamed: R8.2, U2.7 (D2), U2#2.7 (D2)
unnamed: R9.2, U2.8 (D3), U2#2.8 (D3)
unnamed: R10.2, U2.13 (D4), U2#2.13 (D4)
unnamed: R29.1, U12.10 (RBIAS)
unnamed: R32.1, U14.8 (EQ0)
unnamed: R33.1, U14.2 (EQ1)
unnamed: R34.1, U14.22 (DDC_EN)
unnamed: R35.1, U14.3 (DDET)
unnamed: R36.2, U14.4 (REXT)
unnamed: J15.2, SW2.3 (C)
unnamed: U5.1, U8.2 (O0)
unnamed: U5.3, U8.5 (O1)
unnamed: U8.16 (O6), U10.1
unnamed: U9.5 (O1), U10.3
unnamed: U8.6 (O2), U10.5
unnamed: U8.9 (O3), U10.9
unnamed: U8.12 (O4), U10.11
unnamed: U8.15 (O5), U10.13
unnamed: U9.2 (O0), U11.1
unnamed: U9.16 (O6), U11.3
unnamed: U9.6 (O2), U11.5
unnamed: U9.9 (O3), U11.9
unnamed: U9.12 (O4), U11.11
unnamed: U9.15 (O5), U11.13
SDCARD_CD_SW: P1.10 (CD_SWITCH), R31.1, U17.13 (D4)
SDCARD_CLK: J5.56, P1.5 (CLK)
SDCARD_CMD: J5.54, P1.2 (CMD)
SDCARD_D0: J5.58, P1.7 (DAT0)
SDCARD_D1: J5.60, P1.8 (DAT1)
SDCARD_D2: J5.50, P1.9 (DAT2)
SDCARD_D3: J5.52, P1.1 (DAT3/CD)
SDCARD_WP_SW: P1.13 (WP_SWITCH), R30.1, U17.8 (D3)
UART_RX: J4.38, J28.3, JB1.3
UART_TX: J4.40, J28.2, JB1.7
VGA_B0: J4.54, R79.1
VGA_B1: J4.52, R78.1
VGA_B2: J4.50, R77.1
VGA_B3: J4.48, R76.1
VGA_B4: J4.46, R75.1
VGA_B5: J4.44, R74.1
VGA_G0: J4.59, R73.1
VGA_G1: J4.57, R72.1
VGA_G2: J4.55, R71.1
VGA_G3: J4.53, R70.1
VGA_G4: J4.51, R69.1
VGA_G5: J4.49, R68.1
VGA_HSYNC: J4.56, R80.2
VGA_R0: J4.47, R67.1
VGA_R1: J4.45, R66.1
VGA_R2: J4.43, R65.1
VGA_R3: J4.41, R64.1
VGA_R4: J4.39, R63.1
VGA_R5: J4.37, R62.1
VGA_VSYNC: J4.58, R81.2
microSD_CD_Switch: J9.9 (CD_SWITCH1), R37.1, U17.14 (D5)
microSD_CLK: J4.10, J9.5 (CLOCK)
microSD_CMD: J4.12, J9.3 (COMMAND/RESPONSE)
microSD_D0: J4.7, J9.7 (DATA_LINE[BIT_0])
microSD_D1: J4.9, J9.8 (DATA_LINE[BIT_1])
microSD_D2: J4.11, J9.1 (DATA_LINE[BIT_2])
microSD_D3: J4.8, J9.2 (CARD_DETECT/DATA_LINE[BIT_3])

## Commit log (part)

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2022-10-12 begin working on MEGA65CR (cost reduced) R1 schematic
2022-10-12 add IEC port connector and footprint
2022-10-12 complete IEC and 34-pin floppy interface sheet
2022-10-12 refactor floppy circuits onto own sheet
2022-10-12 add files to track local libraries
2022-10-12 add joystick sheet
2022-10-12 fix footprints and update PCB
2022-10-12 add stubs for missing sheets
2022-10-12 add sheets for expansion port, userport, VGA and multiplexor bus
2022-10-12 instantiate 3-8 decoders for MUX
2022-10-12 fix signal directions
2022-10-12 select latches for mux
2022-10-13 rework floppy buffers to use mux bus
2022-10-13 fix joystick input to use mux correctly
2022-10-13 fix joystick outputs to use mux bus
2022-10-13 reformat joystick sheet
2022-10-13 add reset button
2022-10-13 add digital video connectors and JTAG/UART header
2022-10-13 add symbol and footprint for power connector
2022-10-13 finish implementing 5V power supply
2022-10-13 add header for +5V to QMTECH WUKONG FPGA board
2022-10-13 add notes for other ports
2022-10-14 create symbols for C64 tape, user and expansion ports
2022-10-14 begin implementing tape port. add symbols for C64 ports
2022-10-14 connect missing IEC outputs
2022-10-14 add no-connects to various unused pins
2022-10-14 setup pins on userport, but not yet connected to mux bus
2022-10-14 create footprint for userport edge connector
2022-10-14 reformat userport sheet
2022-10-14 place expansion port and set footprint
2022-10-14 work on expansion port
2022-10-14 DOTCLOCK fed via 74LS04 to perform fast level conversion
2022-10-14 add footprint for dipswitch
2022-10-14 work on ethernet
2022-10-14 update eth phy symbol
2022-10-14 add footprint for ferrite bead, work on eth phy
2022-10-15 work on digital video output
2022-10-15 add RTC I2C header
2022-10-15 convert legacy library to make writeable
2022-10-15 add new HDMI buffer chip and footprint
2022-10-15 switch to same HDMI helper chip as on MEGA65 R4 PCB
2022-10-15 hook up expansion port using MUX bus
2022-10-15 add VGA connector and resistor DACs
2022-10-15 add resistor laddars for 3.5mm audio and component video outputs
2022-10-15 add 3.5mm audio jack
2022-10-15 add reversable audio header, e.g., for internal speakers + amp
2022-10-15 add connectors and FPGA pin descriptions for QMTECH K345T board
2022-10-15 plumb all direct FPGA signals.
2022-10-15 beautify the schematics, especially the title-page
2022-10-15 add all missing footprints
2022-10-16 start routing joystick mezzannine
2022-10-16 finish laying out joystick mezzannine PCB
2022-10-16 tweak mezzannine board dimensions
2022-10-16 replace 74LS373s with 74LS374s #5
2022-10-16 replace remaining 74LS373 with 74LS374s #5
2022-10-16 make R/W signals on cart port open-collector with pullup #6
2022-10-16 add missing power switch #7
2022-10-16 correct position of power input and switch and cart port
2022-10-16 further fix cart port and power switch connections #2
2022-10-16 correct port positions and cutouts #2
2022-10-17 add missing MEGA65 keyboard connector and keyboard JTAG header #10 #12
2022-10-17 add USB blaster JTAG and bare UART headers #11
2022-10-17 add C64 keyboard connector on MUX bus #9
2022-10-17 place some mounting holes and reset button #3
2022-10-17 add and position mounting holes #3
2022-10-17 rearrange FPGA board connectors to detangle. Begin routing HDMI
2022-10-17 Replace HDMI connector #13
2022-10-17 route HDMI connector to HDMI helper chip #13
2022-10-18 route eth pairs, add GND planes
2022-10-18 finish routing VGA connector
2022-10-18 layout more of HDMI and ETH and surrounding areas
2022-10-18 route microSD card
2022-10-18 hook up audio DAC busses
2022-10-18 place power suppl
2022-10-18 show R values in symbols on silkscreen
2022-10-18 route joystick ports and pullups etc
2022-10-18 add missing C64 keyboard footprint
2022-10-18 route keyboard
2022-10-18 add missing footprints
2022-10-19 try placing cart port ICs
2022-10-19 route cart port to resistor packs
2022-10-19 begin routing mux bus
2022-10-19 more cart and mux bus layout
2022-10-19 more routing cart + mux bus
2022-10-19 more cart/mux bus routing
2022-10-20 route IEC port. Remove duplicate footprints
2022-10-20 fix many design rule violations
2022-10-20 renumber MUX registers to ease routing
2022-10-21 route more cart port
2022-10-21 more routing cart port
2022-10-21 finish routing middle row of cart ICs
2022-10-21 route u4
2022-10-21 more routing
2022-10-21 route mux bus to C64 keyboard
2022-10-21 add cut-outs for floppy cables #15
2022-10-21 de-overlap U3 from its neighbour
2022-10-21 route SD card resistors
2022-10-21 route hi MUX address lines
2022-10-21 place floppy components and remove redundant resistors
2022-10-21 switch DIP8 to DIP4 using spare pins on floppy MUX R unit
2022-10-22 finish routing floppy corner
2022-10-22 relocate pins to connect RTC I2C
2022-10-22 connect RTC
2022-10-22 fix Jtag enable for keyboard
2022-10-22 place and route JTAG and serial headers
2022-10-22 place and route remaining eth passives
2022-10-22 add symbol and footprint for mini-DIN8 for 1565
2022-10-22 add 1565 interface #14
2022-10-22 route 1565 and tape connectors #14
2022-10-22 work on routing user port
2022-10-22 more work on routing user port and 1565 lines #14
2022-10-22 finish placing mux out bus
2022-10-22 more work on routing user port and tape port signals
2022-10-22 yet more routing
2022-10-22 only 2 more traces to route!
2022-10-22 initial complete routing
2022-10-22 fix most design rule violations
2022-10-22 fix overlapping courtyards
2022-10-22 resolve all real design rule violations
2022-10-22 rotate U24 around the right way
2022-10-22 add footprints to differentiate 3.3V from 5V ICs
2022-10-23 try to fix B.silk, add VIN to +12V_FUSED jumper
2022-10-23 Increase power trace width on joystick mezzannine #8
2022-10-23 fix design rule violations
2022-10-23 fix many DRC warnings
2022-10-23 add improved DIP footprints for smaller packages
2022-10-23 finish solving DRC violations
2022-10-23 exclude HDMI helper chip clearance violations
2022-10-23 add logos and explanatory text
2022-10-23 begin writing utility to create merged BOM from PCB
2022-10-23 scan parts list
2022-10-23 find more parts from BOM
2022-10-23 more BOM parts cataloging
2022-10-23 add power-bypass, fix DRC violation, U29 is 5V VCC
2022-10-24 address #21 and #22
2022-10-24 resolve all items in BoM
2022-10-24 update schematic due to BoM requirements
2022-10-26 consistenly call the board the MEGA65 CR R1, not MEGA65 R5
2022-10-26 begin renaming project to use as basis for r3 expansion board
2022-10-26 continue renaming project
2022-10-26 rework user port
2022-10-26 reconnect everything and add PMOD and 34pin floppy connectors
2022-10-26 begin placing and routing
2022-10-27 fix U30 VCC and footprint
2022-10-29 route many more signals
2022-10-30 finish routing signals
2022-10-30 shrink board, resolve all DRC errors, add openhardware logo
2022-10-30 add github URL to silkscreen
2022-10-30 add silkscreen to FDD connectors. Tweak some tracks.
2022-10-30 finalise for PCBWay initial prototyping
2022-10-31 update master sheet for schematics
2022-10-31 correct stale board ID
2022-10-31 begin working on bom.md
2022-10-31 Fill in list of components.
2022-11-01 Categorize all components.
2022-11-01 Fix typo in part number.
2022-11-01 replot after userport fix
2022-11-03 fix designation of 3.3V ICs
2022-11-07 add current limiting resistors to allow 74HC165 #1
2022-11-07 work on rerouting board to fit current limiting resistors #1
2022-11-07 continue routing current limiting resistors #1
2022-11-26 update footprint cache
2022-11-26 commit unsaved changes related to previous commit
2022-11-26 Address #8, #6, #3
2022-11-26 tweak ground pour for last commit
2022-11-26 fix #7
2022-11-26 fix #4
2022-11-27 fix #2 and generally tidy traces
2023-04-03 pcbway revC order 20230404
2023-12-15 begin work on revD based on corrections to revC
2024-01-07 fix spi1_o -> sp1_o and route net
2024-01-09 remove duplicate plumbing for CNT1
2024-01-09 tidy up schematic trace
2024-01-11 /PC2 is output only
2024-01-11 remote more redundant nets
2024-01-12 add pin 1 markers for TE0790
2024-01-12 relocate TE0790 connector for better fit. Match M65 board depth
2024-01-12 add 3.3V zener to tape sense input
2024-01-12 connect tape GND pin to GND
2024-01-12 add pullups for TAPE_SENSE and TAPE_READ
2024-01-12 move vias away from silkscreen
2024-01-13 add de-coupling cap to U1
2024-01-13 add decoupling cap to U2
2024-01-13 add decoupling cap to U3
2024-01-13 add decoupling cap to U4
2024-01-13 add decoupling cap to U5
2024-01-13 add U6 and U7 decoupling caps
2024-01-13 add U9 U10 decoupling caps
2024-01-13 add U11 decoupling cap
2024-01-13 remove old Zener diode info
2024-01-13 revert PCB size to original
2024-01-13 remove decoupling cap rear silkscreen. add 5V labels
2024-01-13 connect PA2_EN, make open-collector
2024-01-13 correct hole positions
2024-01-14 begin work on PMOD link PCB
2024-01-14 add board cut-out
2024-01-14 add GND and 3.3V planes
2024-01-14 fix pad numbering
2024-01-14 finish place and route. Reduce board size
2024-01-14 use 3rd channel for video, not audio
2024-01-14 move TE0790 relay socket nearer to MEGA65 board
2024-01-14 make 5V rail 1mm track
2024-01-14 branch 5V as much as possible
2024-01-14 branch 3.3V
2024-01-15 begin designing board to connect M65 to exp board
2024-01-15 update connector positions for bridge board
2024-01-15 trim board size
2024-01-15 export gerbers and final tidy up
2024-01-22 correct PMOD placement on connector PCB
2024-01-22 fix connector placement on bridge board
2024-01-23 reduce connector board to 2-layer for faster fabrication
2024-01-23 add dimensional measurements to pmod connector
2024-02-03 commit unknown change that was hanging around
2024-02-03 move J13 and H3 and H9
2024-02-03 switch to 2 pin resistor ladders
2024-02-03 reduce video output impedence from 500 to 250 Ohms
2024-02-03 work on re-routing JTAG area etc
2024-02-03 more work re-routing
2024-02-03 revert JTAG footprints to having all pins
2024-02-03 tidy up some traces and remaining warnings
2024-02-04 move PMODs 1mm down. Expand board bottom to support PMODs
2024-02-04 move R21 away from floppy chassis
2024-02-04 finish moving PMODs and R21
2024-02-04 flip J8 and relocate
2024-02-04 fill-out size of bridge board to fit wifi etc
2024-02-04 work on various checking various measurements
2024-02-04 add lots of measurement marks for bridge board
2024-02-04 move PMODs on expansion board left 0.51mm
2024-02-04 update floppy header names to match underlying boards
2024-02-04 add ESP32 component libraries
2024-02-04 update to kicad 7. begin adding ESP32
2024-02-06 add more pins to peripheral header. Reorder
2024-02-18 add remaining connectors to bridge board
2024-02-23 add matched position ESP32 connector on expansion board
2024-02-23 tidy up routing a bit
2024-02-23 remove obsoleted note
2024-02-23 plumb WIFI_EN line
2024-02-23 direct C1565_SERIO, C1565_LD outputs
2024-02-23 begin adding missing C1565 signal buffers
2024-02-24 fix design rule check errors and false alarms
2024-02-24 fix and finish routing 3.3V SERIO and related things
2024-02-24 fatten 3.3V rail part of its length
2024-02-24 begin peeling out C1565 port to separate sheet
2024-02-25 reroute 1565 clock, LD and 5V WIFI_EN line
2024-02-25 document WIFI_EN, tidy up a bit more
2024-02-25 import mini-din 9 footprint and symbol
2024-02-25 add A/V filter circuits and audio links to bridge board
2024-02-25 route filters for other video channels
2024-02-25 video filter routing and DRC good
2024-02-25 final tidy ups
2024-02-25 add MEGA65 and open hardware logos etc
2024-02-25 add audio J19 pickup header
2024-02-25 begin working on C1565 PCB
2024-02-25 dont include backups in repo
2024-02-25 add more logic to C1565 board
2024-02-25 begin work on layout
2024-02-25 fix floating gate inputs
2024-02-25 gerbers exported and uploaded to pcbway
2024-02-28 add dipsw reading to M1565 via spare bit
2024-02-28 route +5V and GND on M1565 board
2024-02-29 more work on M1565 board
2024-03-22 more work on external drive board
2024-03-29 finish M1565 initial board rev
